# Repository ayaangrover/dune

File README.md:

# dune
a wireless low profile hotswap split keyboard

## What it is
Dune is a low profile hotswap wireless split keyboard with ZMK support. 

## Why I made it
I made it because I want to do my homework in my notebook but also be able to type and use my mouse. this way i can place my notebook between the two halves of my keyboard.

## Models
Case models are in /Case, case + pcb and just pcb models are both in /Dune.

## Images

## Bom

I'm printing [these](https://makerworld.com/en/models/2011079-low-profile-choc-v2-17mm-keycap?from=search#profileId-2166451) keycaps for the keyboard.

| Item | Description | Cost (USD) | Link |
|------|-------------|------------|------|
| Switches | Kailh Choc Round Brown 45g (Low-Profile Tactile) | $20.18 | https://mechanicalkeyboards.com/products/kailh-choc-round-brown-45g-low-profile-tactile?variant=50919348699436 |
| Keycaps | 3D printed | $0.00 | https://makerworld.com/en/models/2011079-low-profile-choc-v2-17mm-keycap?from=search#profileId-2166451 |
| Sockets | Kailh Choc sockets | $8.38 | https://www.aliexpress.us/item/3256806931242093.html |
| MCU | nRF52840 | $8.08 | https://www.aliexpress.us/item/3256805848952479.html |
| Batteries | Li-Po batteries | $8.84 | https://www.aliexpress.us/item/3256807087483508.html |
| PCB | Custom PCB fabrication | $57.58 | https://jlcpcb.com/ |
| **Total** |  | **$103.06(tax)** |  |

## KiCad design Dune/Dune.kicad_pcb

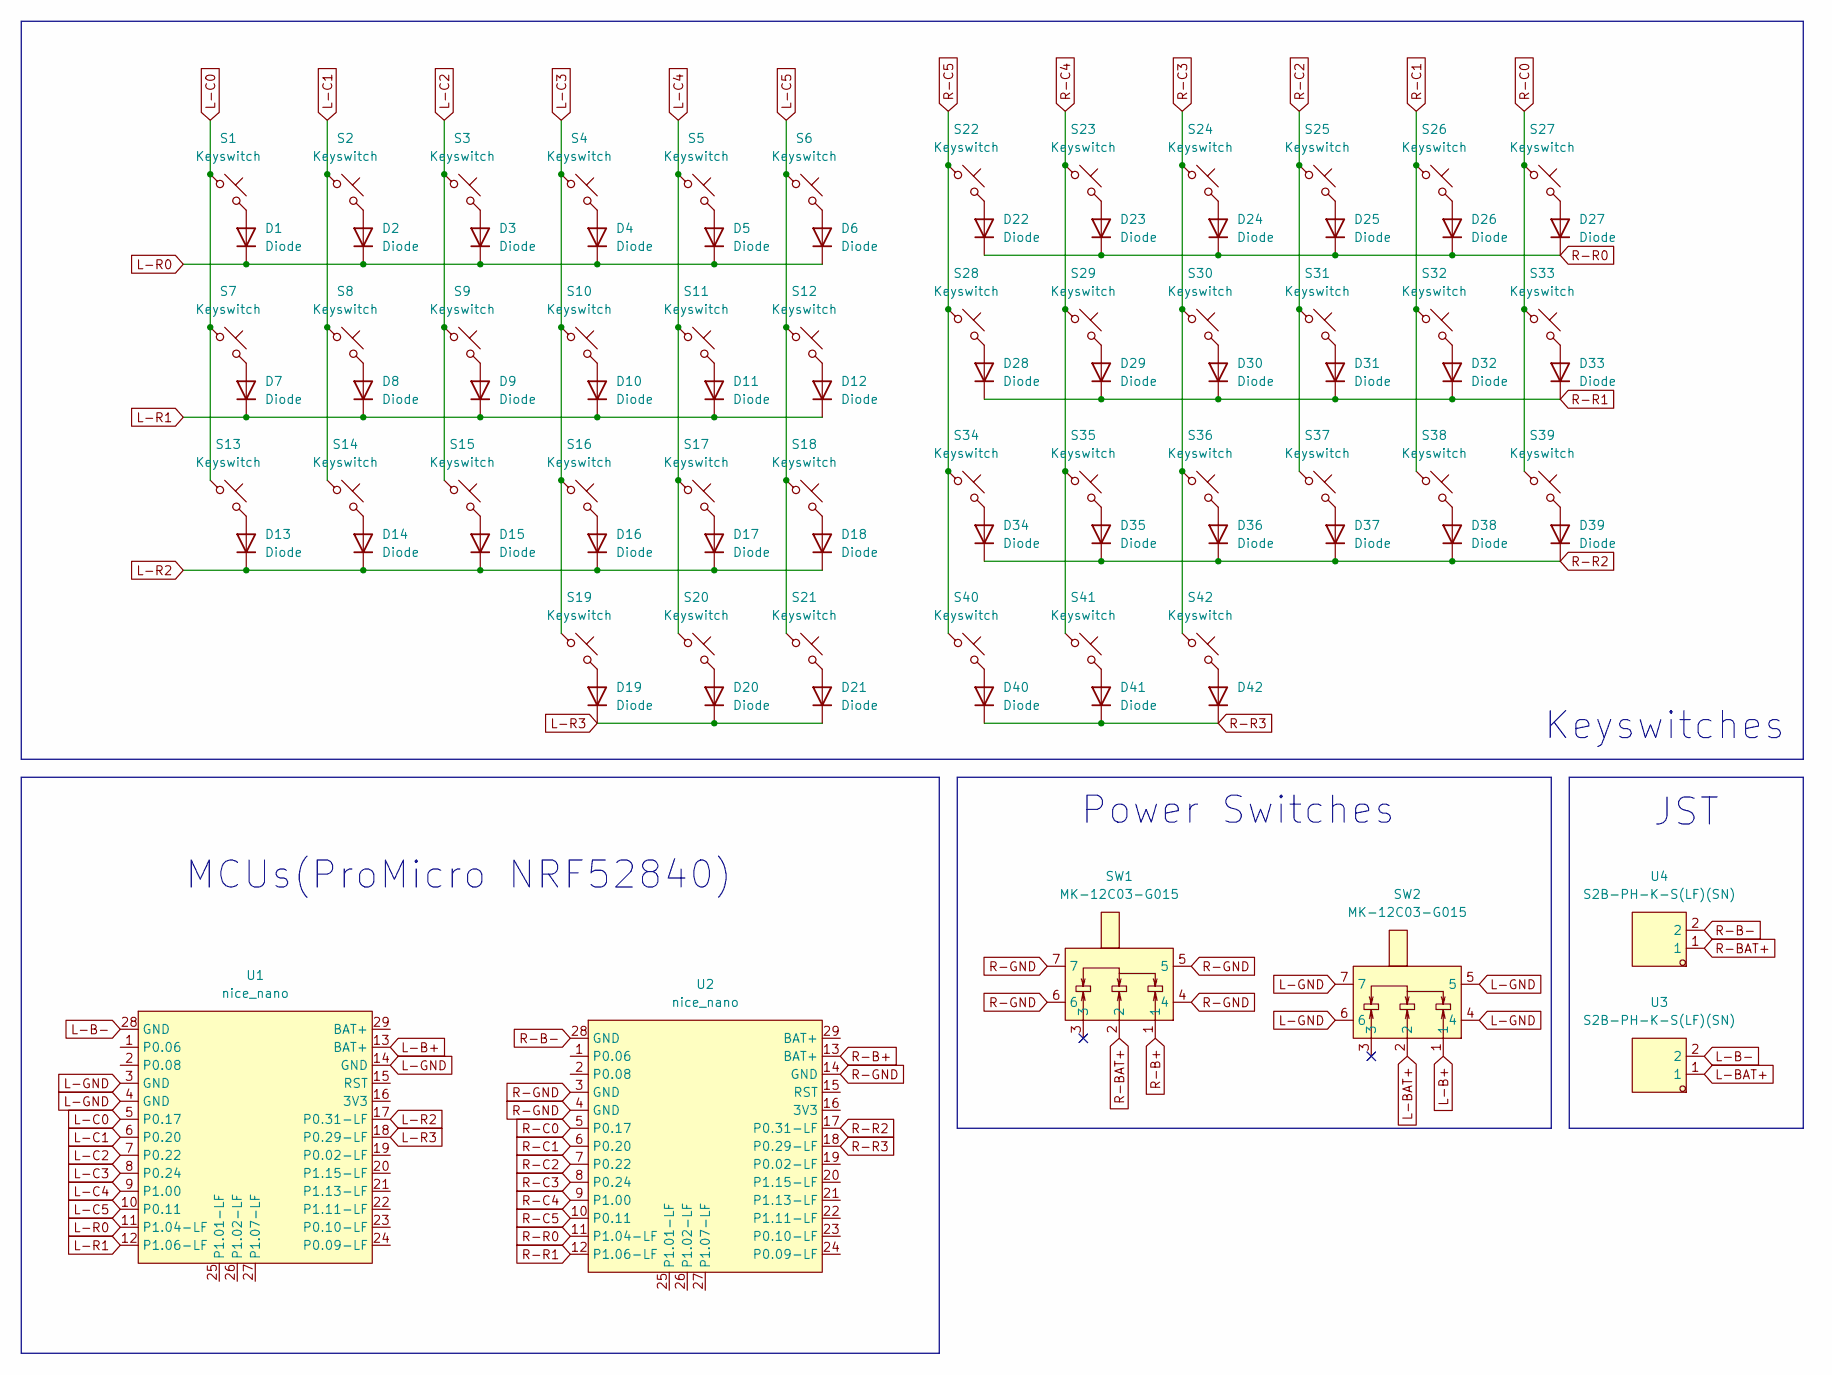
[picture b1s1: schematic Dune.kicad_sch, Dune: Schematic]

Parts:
D1, D2, D3, D4, D5, D6, D7, D8, D9, D10, D11, D12, D13, D14, D15, D16, D17, D18, D19, D20, D21, D22, D23, D24, D25, D26, D27, D28, D29, D30, D31, D32, D33, D34, D35, D36, D37, D38, D39, D40, D41, D42: Diode; Diode_SOD-123
S1, S2, S3, S4, S5, S6, S7, S8, S9, S10, S11, S12, S13, S14, S15, S16, S17, S18, S19, S20, S21, S22, S23, S24, S25, S26, S27, S28, S29, S30, S31, S32, S33, S34, S35, S36, S37, S38, S39, S40, S41, S42: Keyswitch; Hotswap_Choc_V2_1.00u
SW1, SW2: MK-12C03-G015; SW-SMD_MK-12C03-G015; LCSC Part C2890358
U1, U2: nice_nano; SuperMini NRF52840
U3, U4: S2B-PH-K-S(LF)(SN); CONN-TH_S2B-PH-K-S-LF-SN; LCSC Part C173752

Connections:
L-B+: SW2.1, U1.13 (BAT+)
L-B-: U1.28 (GND), U3.2
L-BAT+: SW2.2, U3.1
L-C0: S1.1, S7.1, S13.1, U1.5 (P0.17)
L-C1: S2.1, S8.1, S14.1, U1.6 (P0.20)
L-C2: S3.1, S9.1, S15.1, U1.7 (P0.22)
L-C3: S4.1, S10.1, S16.1, S19.1, U1.8 (P0.24)
L-C4: S5.1, S11.1, S17.1, S20.1, U1.9 (P1.00)
L-C5: S6.1, S12.1, S18.1, S21.1, U1.10 (P0.11)
L-GND: SW2.4, SW2.5, SW2.6, SW2.7, U1.3 (GND), U1.4 (GND), U1.14 (GND)
L-R0: D1.1 (K), D2.1 (K), D3.1 (K), D4.1 (K), D5.1 (K), D6.1 (K), U1.11 (P1.04-LF)
L-R1: D7.1 (K), D8.1 (K), D9.1 (K), D10.1 (K), D11.1 (K), D12.1 (K), U1.12 (P1.06-LF)
L-R2: D13.1 (K), D14.1 (K), D15.1 (K), D16.1 (K), D17.1 (K), D18.1 (K), U1.17 (P0.31-LF)
L-R3: D19.1 (K), D20.1 (K), D21.1 (K), U1.18 (P0.29-LF)
unnamed: D1.2 (A), S1.2
unnamed: D2.2 (A), S2.2
unnamed: D3.2 (A), S3.2
unnamed: D4.2 (A), S4.2
unnamed: D5.2 (A), S5.2
unnamed: D6.2 (A), S6.2
unnamed: D7.2 (A), S7.2
unnamed: D8.2 (A), S8.2
unnamed: D9.2 (A), S9.2
unnamed: D10.2 (A), S10.2
unnamed: D11.2 (A), S11.2
unnamed: D12.2 (A), S12.2
unnamed: D13.2 (A), S13.2
unnamed: D14.2 (A), S14.2
unnamed: D15.2 (A), S15.2
unnamed: D16.2 (A), S16.2
unnamed: D17.2 (A), S17.2
unnamed: D18.2 (A), S18.2
unnamed: D19.2 (A), S19.2
unnamed: D20.2 (A), S20.2
unnamed: D21.2 (A), S21.2
unnamed: D22.2 (A), S22.2
unnamed: D23.2 (A), S23.2
unnamed: D24.2 (A), S24.2
unnamed: D25.2 (A), S25.2
unnamed: D26.2 (A), S26.2
unnamed: D27.2 (A), S27.2
unnamed: D28.2 (A), S28.2
unnamed: D29.2 (A), S29.2
unnamed: D30.2 (A), S30.2
unnamed: D31.2 (A), S31.2
unnamed: D32.2 (A), S32.2
unnamed: D33.2 (A), S33.2
unnamed: D34.2 (A), S34.2
unnamed: D35.2 (A), S35.2
unnamed: D36.2 (A), S36.2
unnamed: D37.2 (A), S37.2
unnamed: D38.2 (A), S38.2
unnamed: D39.2 (A), S39.2
unnamed: D40.2 (A), S40.2
unnamed: D41.2 (A), S41.2
unnamed: D42.2 (A), S42.2
R-B+: SW1.1, U2.13 (BAT+)
R-B-: U2.28 (GND), U4.2
R-BAT+: SW1.2, U4.1
R-C0: S27.1, S33.1, S39.1, U2.5 (P0.17)
R-C1: S26.1, S32.1, S38.1, U2.6 (P0.20)
R-C2: S25.1, S31.1, S37.1, U2.7 (P0.22)
R-C3: S24.1, S30.1, S36.1, S42.1, U2.8 (P0.24)
R-C4: S23.1, S29.1, S35.1, S41.1, U2.9 (P1.00)
R-C5: S22.1, S28.1, S34.1, S40.1, U2.10 (P0.11)
R-GND: SW1.4, SW1.5, SW1.6, SW1.7, U2.3 (GND), U2.4 (GND), U2.14 (GND)
R-R0: D22.1 (K), D23.1 (K), D24.1 (K), D25.1 (K), D26.1 (K), D27.1 (K), U2.11 (P1.04-LF)
R-R1: D28.1 (K), D29.1 (K), D30.1 (K), D31.1 (K), D32.1 (K), D33.1 (K), U2.12 (P1.06-LF)
R-R2: D34.1 (K), D35.1 (K), D36.1 (K), D37.1 (K), D38.1 (K), D39.1 (K), U2.17 (P0.31-LF)
R-R3: D40.1 (K), D41.1 (K), D42.1 (K), U2.18 (P0.29-LF)

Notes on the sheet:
MCUs(ProMicro NRF52840)
JST
Keyswitches
Power Switches

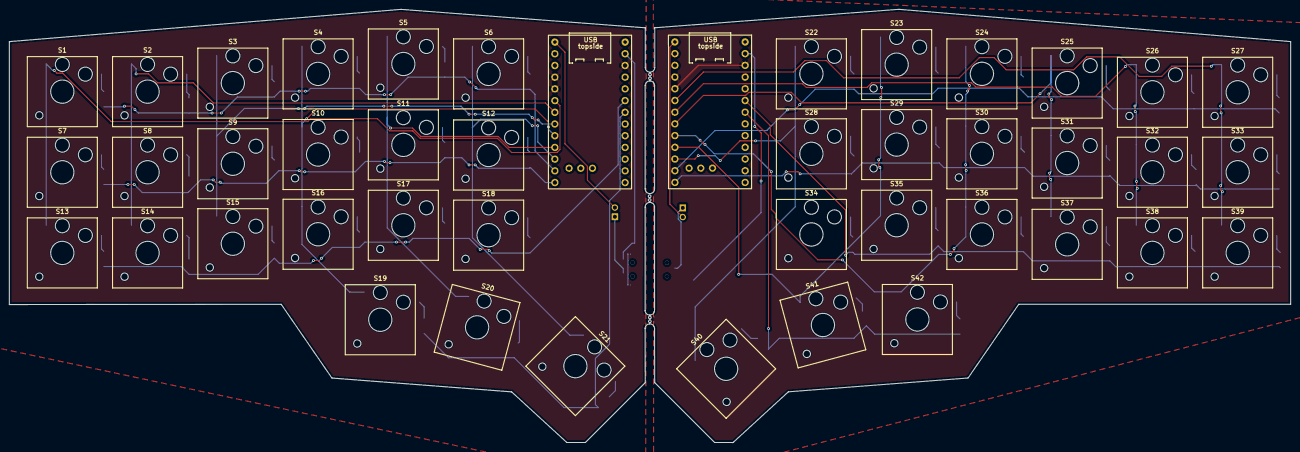
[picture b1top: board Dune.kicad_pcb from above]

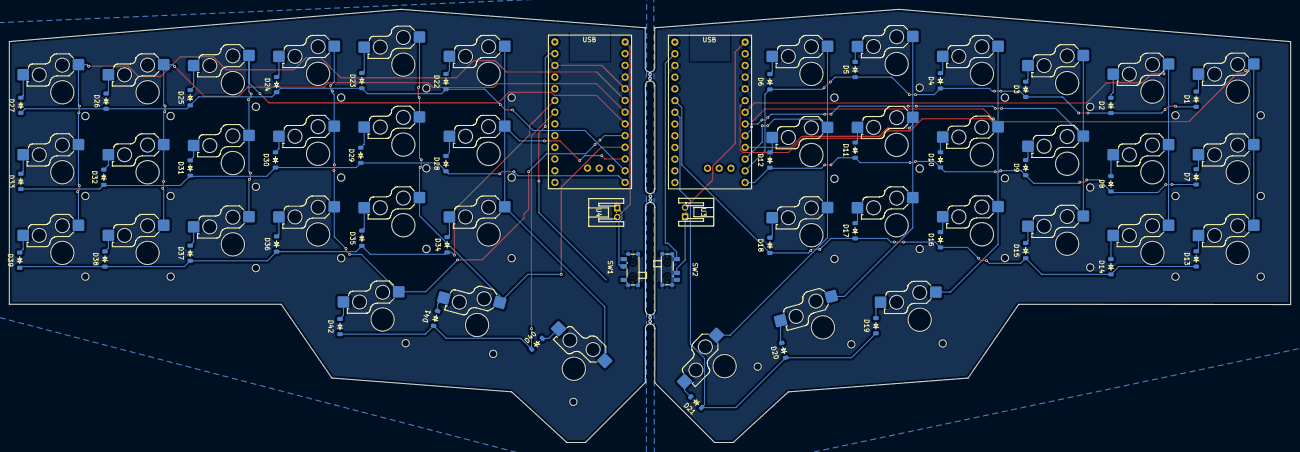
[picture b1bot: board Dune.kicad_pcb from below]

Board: 2 copper layers, 278.0 x 94.0 mm, 90 parts (46 on the bottom side), 70 nets.

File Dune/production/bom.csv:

Designator,Footprint,Quantity,Value,LCSC Part #
"D1, D10, D11, D12, D13, D14, D15, D16, D17, D18, D19, D2, D20, D21, D22, D23, D24, D25, D26, D27, D28, D29, D3, D30, D31, D32, D33, D34, D35, D36, D37, D38, D39, D4, D40, D41, D42, D5, D6, D7, D8, D9",Diode_SOD-123,42,Diode,
"S1, S10, S11, S12, S13, S14, S15, S16, S17, S18, S19, S2, S20, S21, S22, S23, S24, S25, S26, S27, S28, S29, S3, S30, S31, S32, S33, S34, S35, S36, S37, S38, S39, S4, S40, S41, S42, S5, S6, S7, S8, S9",Hotswap_Choc_V2_1.00u,42,Keyswitch,
"SW1, SW2",SW-SMD_MK-12C03-G015,2,MK-12C03-G015,C2890358
"U3, U4",CONN-TH_S2B-PH-K-S-LF-SN,2,S2B-PH-K-S(LF)(SN),C173752

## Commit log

2025-11-02 Add Dune project files with LFS support
2025-11-02 Add Dune.stl
2025-11-25 Add case
2025-12-22 Remove KiCad temporary files from git
2025-12-22 Create bom.csv with item descriptions and costs
    Added bill of materials with item details and costs.
2025-12-22 Add link to Keycaps in bom.csv
2026-01-14 Rename Dune.step to PCB+Keycaps.step
2026-01-19 Add case_right.step file
